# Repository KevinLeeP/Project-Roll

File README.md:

<h1>Project Roll </h1>
<p1>Project Roll is a spherical robot that achieves omni-directional movement using omni-wheels and a hamster ball drive mechanism. The robot features a custom Smart Power Distribution Board made in KiCAD that centralizes power management and connections between sensors, motors, and ESP-32 MCU onto one board. The software written in C++ is currently a work in progress.</p1>

## OnShape CAD
[Onshape Link](https://cad.onshape.com/documents/6bff8405cef2444ed844f4c5/w/1237cbf75ed8744d7832d4f6/e/41b5c13e098610f260b44efa?renderMode=0&uiState=6a694b24ff56974464881385)

## Images

<p1> Custom power distribution board </p1>

<p1> Robot CAD showing internals </p1>

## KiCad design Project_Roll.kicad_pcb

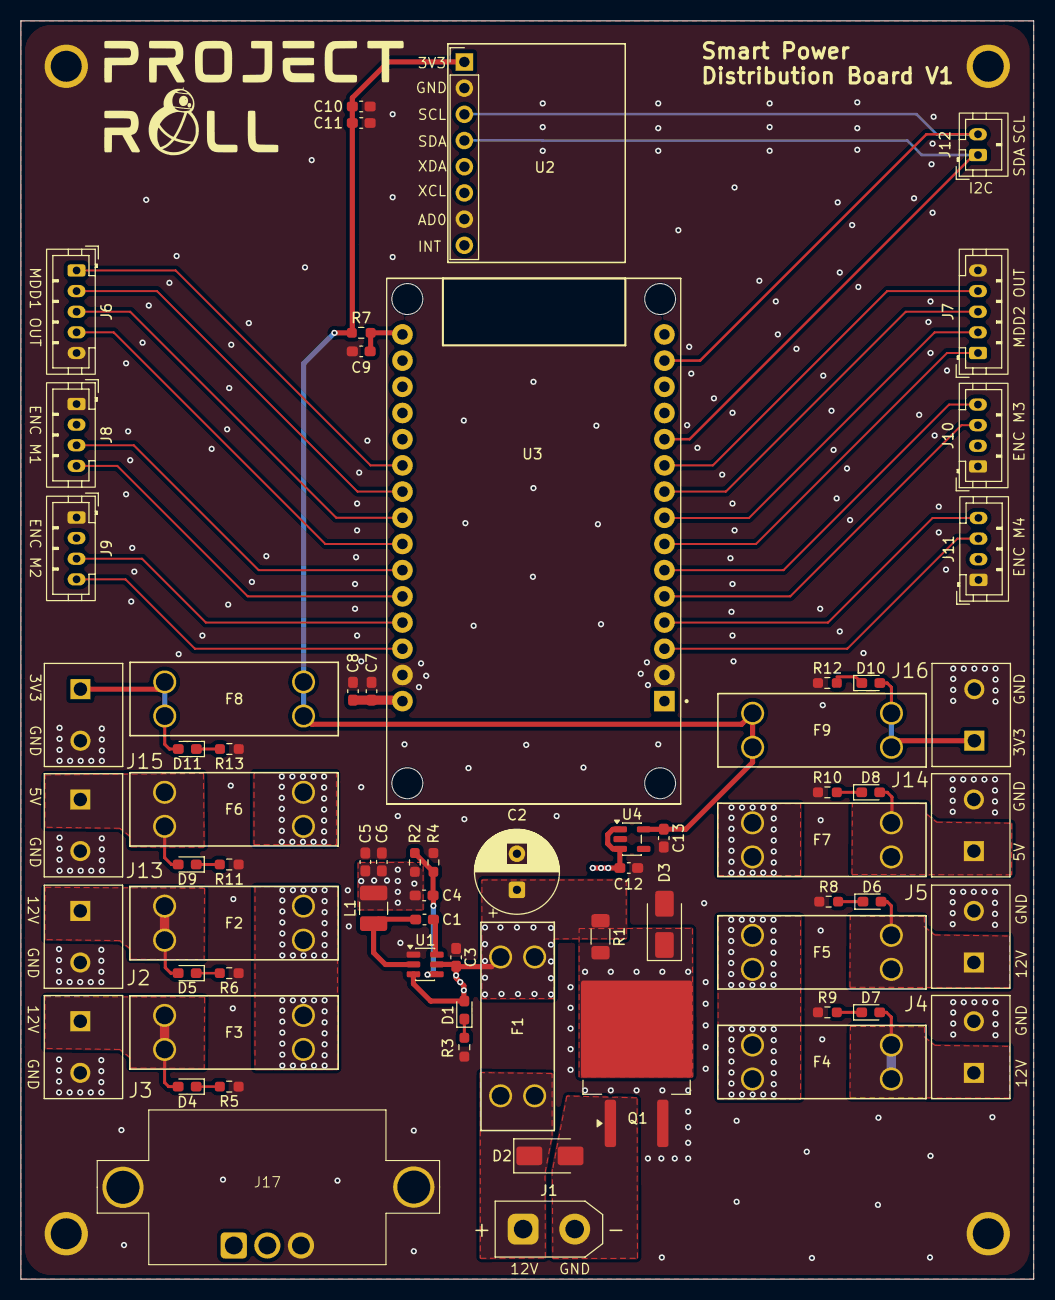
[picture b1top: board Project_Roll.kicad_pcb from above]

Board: 4 copper layers, 98.2 x 122.0 mm, 73 parts (0 on the bottom side), 46 nets.

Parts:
C1, C8, C11: 0.1uF; C_0603_1608Metric_Pad1.08x0.95mm_HandSolder
C2: 220uF; CP_Radial_D8.0mm_P3.50mm
C3: 10uF; C_0603_1608Metric_Pad1.08x0.95mm_HandSolder
C4: 10pF; C_0603_1608Metric_Pad1.08x0.95mm_HandSolder
C5, C6: 22uF; C_0603_1608Metric_Pad1.08x0.95mm_HandSolder
C7, C9, C10, C12, C13: 1uF; C_0603_1608Metric_Pad1.08x0.95mm_HandSolder
D1, D4, D5, D6, D7, D8, D9, D10, D11: LTST-C193TBKT-5A; D_0603_1608Metric_Pad1.05x0.95mm_HandSolder
D2: SMAJ15CA; D_SMA
D3: SMAJ15A; D_SMA
F1: 20A; CONN_3557-2_KEY
F2, F3, F4, F5, F6, F7, F8, F9: 10A; CONN_3557-2_KEY
H1, H2, H3, H4: MountingHole_Pad; MountingHole_3.2mm_M3_DIN965_Pad
J1: TB002-500-02BE; AMASS_XT30UPB-F_1x02_P5.0mm_Vertical
J2, J3, J4, J5, J13, J14, J15, J16: TB002-500-02BE; CUI_TB002-500-02BE
J6, J7: Conn_01x05; JST_PH_B5B-PH-K_1x05_P2.00mm_Vertical
J8, J9, J10, J11: Conn_01x04; JST_PH_B4B-PH-K_1x04_P2.00mm_Vertical
J12: Conn_01x02; JST_PH_B2B-PH-K_1x02_P2.00mm_Vertical
J17: Conn_01x03; Voltage Meter
L1: 3.3uH; L_1210_3225Metric_Pad1.42x2.65mm_HandSolder
Q1: IRFS7430TRLPBF; TO-263-2
R1: 10k; R_1206_3216Metric_Pad1.30x1.75mm_HandSolder
R2: 56.2k; R_0603_1608Metric_Pad0.98x0.95mm_HandSolder
R3, R5, R6, R8, R9: 2k; R_0603_1608Metric_Pad0.98x0.95mm_HandSolder
R4, R7: 10k; R_0603_1608Metric_Pad0.98x0.95mm_HandSolder
R10, R11: 620; R_0603_1608Metric_Pad0.98x0.95mm_HandSolder
R12, R13: 270; R_0603_1608Metric_Pad0.98x0.95mm_HandSolder
U1: AP62300TWU; TSOT-23-6
U2: GY-521; PinHeader_1x08_P2.54mm_Vertical
U3: ESP32-DEVKIT-V1; MODULE_ESP32_DEVKIT_V1
U4: MIC5504-3.3YM5; SOT-23-5

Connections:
+3V3: C10.1, C11.1, C13.1, F8.1, F9.1, R7.1, U2.1 (VCC), U4.5 (VOUT)
+5V: C4.1, C5.1, C6.1, C7.1, C8.1, C12.1, F6.1, F7.1, J8.2, J9.2, J10.2, J11.2, L1.2, R2.1, U3.30 (VIN), U4.1 (VIN), U4.3 (EN)
+12V: C2.1, C3.1, D1.2 (A), F1.2, F2.1, F3.1, F4.1, F5.1, J17.1, J17.2, R1.1, U1.3 (IN), U1.5 (EN)
GND: C2.2, C3.2, C5.2, C6.2, C7.2, C8.2, C9.2, C10.2, C11.2, C12.2, C13.2, D3.2 (A2), H1.1 (1_1), H2.1 (1_1), H3.1 (1_1), H4.1 (1_1), J2.2, J3.2, J4.2, J5.2, J6.5, J7.5, J8.1, J9.1, J10.1, J11.1, J13.2, J14.2, J15.2, J16.2, J17.3, Q1.3 (S), R3.1, R4.2, R5.1, R6.1, R8.1, R9.1, R10.1, R11.1, R12.1, R13.1, U1.1 (GND), U2.2 (GND), U2.7 (AD0), U3.2 (GND), U3.29 (GND), U4.2 (GND)
GND_BAT: D2.2 (A2), J1.2, Q1.1 (D)
I2C_SCL: J12.2, U2.3 (SCL), U3.14 (D22)
I2C_SDA: J12.1, U2.4 (SDA), U3.11 (D21)
M1_DIR: J6.1, U3.21 (D32)
M1_ENC_A: J8.3, U3.25 (D27)
M1_ENC_B: J8.4, U3.26 (D14)
M1_PWM: J6.2, U3.22 (D33)
M2_DIR: J6.3, U3.23 (D25)
M2_ENC_A: J9.3, U3.27 (D12)
M2_ENC_B: J9.4, U3.28 (D13)
M2_PWM: J6.4, U3.24 (D26)
M3_DIR: J7.1, U3.7 (TX2)
M3_ENC_A: J10.3, U3.5 (D4)
M3_ENC_B: J10.4, U3.6 (RX2)
M3_PWM: J7.2, U3.8 (D5)
M4_DIR: J7.4, U3.10 (D19)
M4_ENC_A: J11.3, U3.3 (D15)
M4_ENC_B: J11.4, U3.4 (D2)
M4_PWM: J7.3, U3.9 (D18)
unnamed: D1.1 (K), R3.2
unnamed: D3.1 (A1), Q1.2 (G), R1.2
unnamed: D4.2 (A), F3.2, J3.1
unnamed: D4.1 (K), R5.2
unnamed: D5.2 (A), F2.2, J2.1
unnamed: D5.1 (K), R6.2
unnamed: D6.2 (A), F5.2, J5.1
unnamed: D6.1 (K), R8.2
unnamed: D7.2 (A), F4.2, J4.1
unnamed: D7.1 (K), R9.2
unnamed: D8.2 (A), F7.2, J14.1
unnamed: D8.1 (K), R10.2
unnamed: D9.2 (A), F6.2, J13.1
unnamed: D9.1 (K), R11.2
unnamed: D10.2 (A), F9.2, J16.1
unnamed: D10.1 (K), R12.2
unnamed: D11.2 (A), F8.2, J15.1
unnamed: D11.1 (K), R13.2
unnamed: C1.1, U1.6 (BST)
unnamed: C4.2, R2.2, R4.1, U1.4 (FB)
unnamed: C1.2, L1.1, U1.2 (SW)
unnamed: C9.1, R7.2, U3.16 (EN)
V_BATT: D2.1 (A1), F1.1, J1.1

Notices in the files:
Project_Roll.kicad_pcb:
2026 Kevin Pfeffer. All rights reserved
